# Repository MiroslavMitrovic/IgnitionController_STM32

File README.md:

# IgnitionController_STM32

## Ignition controller implementation for  4T Single Cylinder/V-Twin motorcycle. 

- Generated documentation is available in .\IgnitionController_STM32\Documentation\Ignition_Controller.chm
- Requirements are available in .\IgnitionController_STM32\Design\Requirements\IgnitionControllerRequriements.txt
- Architecture is done with Rational Software architect, and project is available at .\IgnitionController_STM32\Design\

## Addition of CMake build toolchain 
- Command for build configuration generation is : 
cmake -G "Unix Makefiles" -S . -B build -DCMAKE_BUILD_TYPE="Debug" -DCMAKE_TOOLCHAIN_FILE="arm-none-eabi-gcc.cmake" -DCMAKE_EXPORT_COMPILE_COMMANDS=1 
- Command for build is : 
cmake --build build
## Addition of Static and Dynamic Test Frameworks 
- For Static Code Analysis Mathworks Polyspace Code Prover and Bug finder tools are used 
- For Dynamic(Unit) Testing Google Test Framework is used 
- Setup is available in Testing Folder.

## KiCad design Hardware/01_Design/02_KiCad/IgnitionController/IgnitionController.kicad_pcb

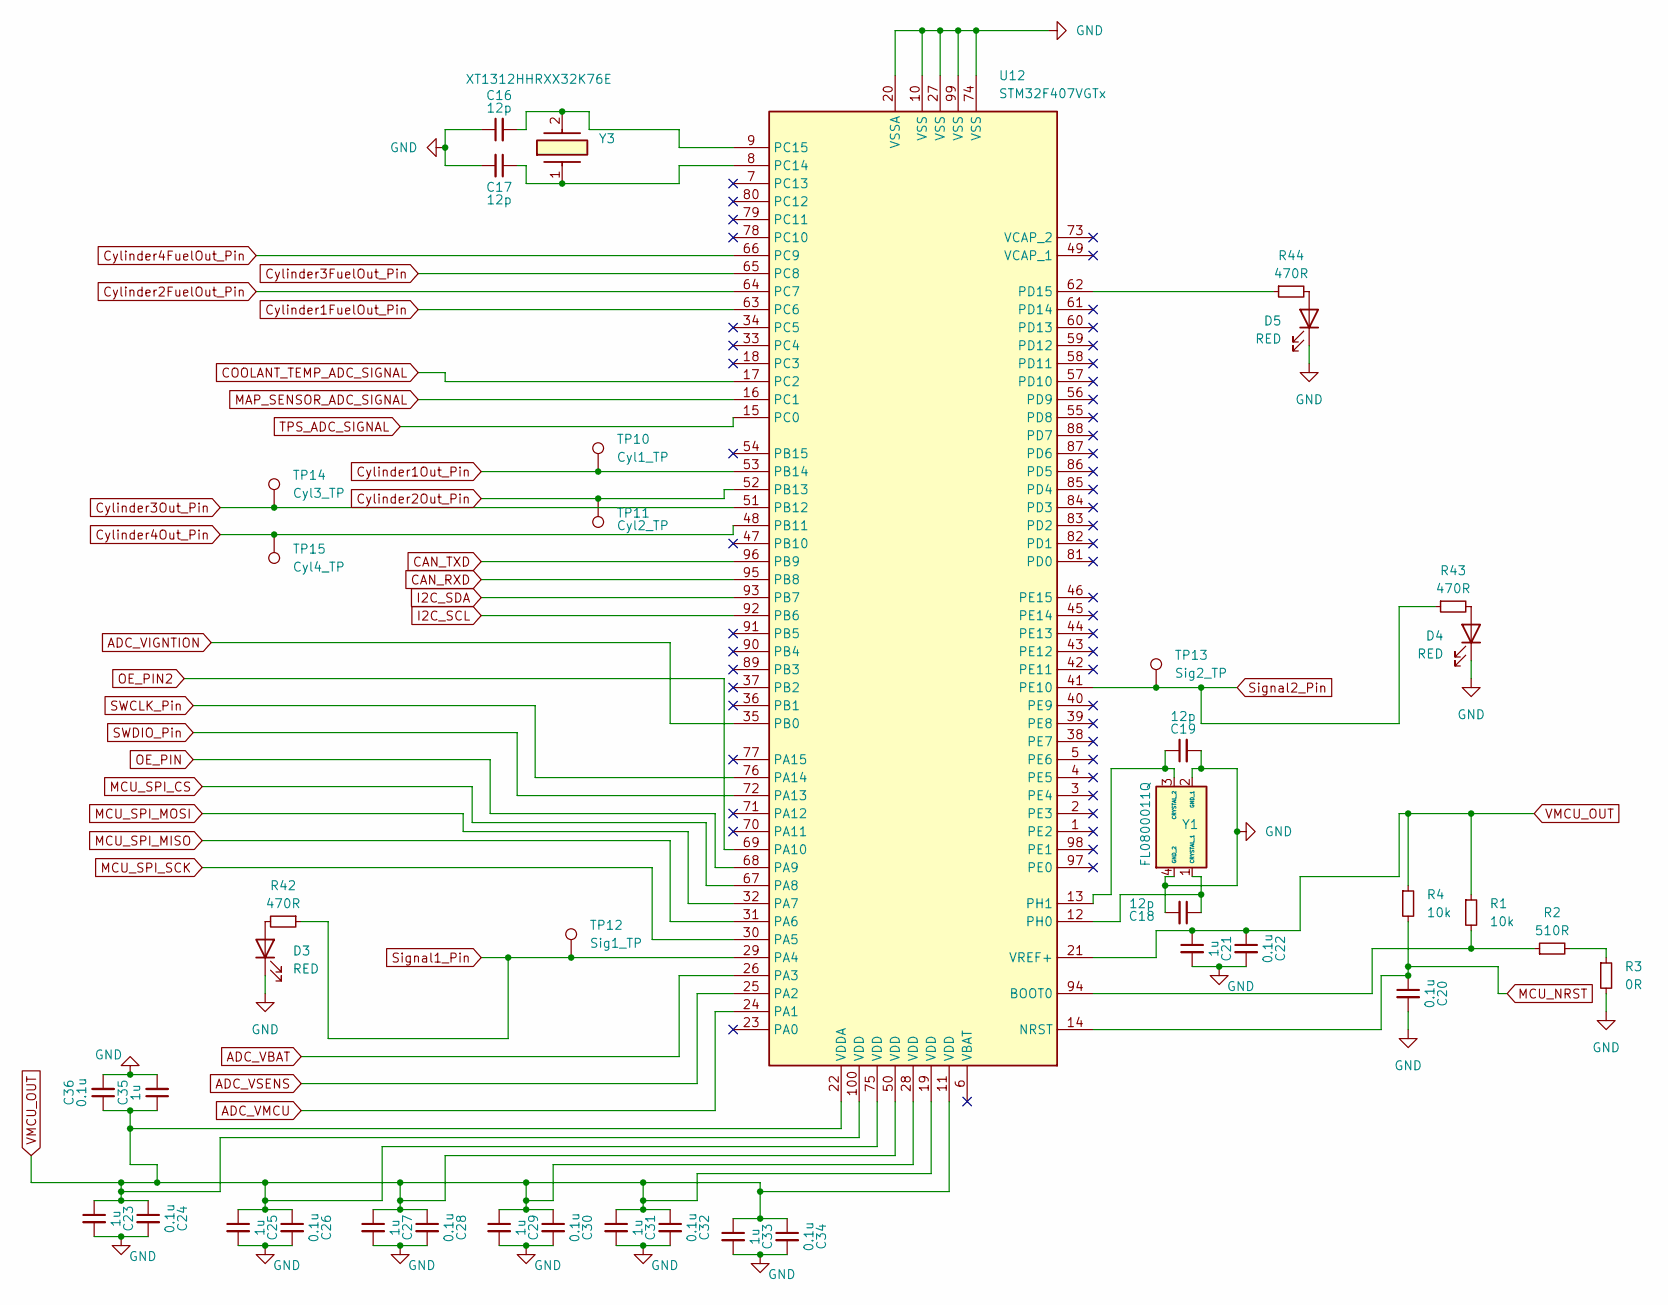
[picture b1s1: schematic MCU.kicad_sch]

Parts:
C16, C17, C18, C19: 12p; C_0603_1608Metric_Pad1.08x0.95mm_HandSolder
C20, C22, C24, C26, C28, C30, C32, C34, C36: 0.1u; C_0603_1608Metric_Pad1.08x0.95mm_HandSolder
C21, C23, C25, C27, C29, C31, C33, C35: 1u; C_0603_1608Metric_Pad1.08x0.95mm_HandSolder
D3, D4, D5: RED; LED_1206_3216Metric_Pad1.42x1.75mm_HandSolder
R1, R4: 10k; R_0603_1608Metric_Pad0.98x0.95mm_HandSolder
R2: 510R; R_0603_1608Metric_Pad0.98x0.95mm_HandSolder
R3: 0R; R_0603_1608Metric_Pad0.98x0.95mm_HandSolder
R42, R43, R44: 470R; R_0603_1608Metric_Pad0.98x0.95mm_HandSolder
TP10: Cyl1_TP; TestPoint_Pad_1.0x1.0mm
TP11: Cyl2_TP; TestPoint_Pad_1.0x1.0mm
TP12: Sig1_TP; TestPoint_Pad_1.0x1.0mm
TP13: Sig2_TP; TestPoint_Pad_1.0x1.0mm
TP14: Cyl3_TP; TestPoint_Pad_1.0x1.0mm
TP15: Cyl4_TP; TestPoint_Pad_1.0x1.0mm
U12: STM32F407VGTx; LQFP-100_14x14mm_P0.5mm
Y1: FL0800011Q; Mouser Part Number 729-FL0800011Q
Y3: XT1312HHRXX32K76E; Mouser Part Number 70-XT1312HHRXX32K76E

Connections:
ADC_VBAT: U12.26 (PA3); also elsewhere on the board
ADC_VIGNTION: U12.35 (PB0); also elsewhere on the board
ADC_VMCU: U12.24 (PA1); also elsewhere on the board
ADC_VSENS: U12.25 (PA2); also elsewhere on the board
CAN_RXD: U12.95 (PB8); also elsewhere on the board
CAN_TXD: U12.96 (PB9); also elsewhere on the board
COOLANT_TEMP_ADC_SIGNAL: U12.17 (PC2); also elsewhere on the board
Cylinder1FuelOut_Pin: U12.63 (PC6); also elsewhere on the board
Cylinder1Out_Pin: TP10.1, U12.53 (PB14); also elsewhere on the board
Cylinder2FuelOut_Pin: U12.64 (PC7); also elsewhere on the board
Cylinder2Out_Pin: TP11.1, U12.52 (PB13); also elsewhere on the board
Cylinder3FuelOut_Pin: U12.65 (PC8); also elsewhere on the board
Cylinder3Out_Pin: TP14.1, U12.51 (PB12); also elsewhere on the board
Cylinder4FuelOut_Pin: U12.66 (PC9); also elsewhere on the board
Cylinder4Out_Pin: TP15.1, U12.48 (PB11); also elsewhere on the board
I2C_SCL: U12.92 (PB6); also elsewhere on the board
I2C_SDA: U12.93 (PB7); also elsewhere on the board
MAP_SENSOR_ADC_SIGNAL: U12.16 (PC1); also elsewhere on the board
MCU_NRST: C20.1, R4.2, U12.14 (NRST); also elsewhere on the board
MCU_SPI_CS: U12.67 (PA8); also elsewhere on the board
MCU_SPI_MISO: U12.31 (PA6); also elsewhere on the board
MCU_SPI_MOSI: U12.32 (PA7); also elsewhere on the board
MCU_SPI_SCK: U12.30 (PA5); also elsewhere on the board
unnamed: D3.2 (A), R42.2
unnamed: D4.2 (A), R43.2
unnamed: D5.2 (A), R44.2
unnamed: R2.2, R3.1
unnamed: R1.2, R2.1, U12.94 (BOOT0)
unnamed: C17.1, U12.8 (PC14), Y3.1
unnamed: C16.2, U12.9 (PC15), Y3.2
unnamed: R44.1, U12.62 (PD15)
unnamed: C19.1, U12.13 (PH1), Y1.3 (CRYSTAL_2)
OE_PIN: U12.68 (PA9); also elsewhere on the board
OE_PIN2: U12.69 (PA10); also elsewhere on the board
SWCLK_Pin: U12.76 (PA14); also elsewhere on the board
SWDIO_Pin: U12.72 (PA13); also elsewhere on the board
Signal1_Pin: R42.1, TP12.1, U12.29 (PA4); also elsewhere on the board
Signal2_Pin: R43.1, TP13.1, U12.41 (PE10); also elsewhere on the board
TPS_ADC_SIGNAL: U12.15 (PC0); also elsewhere on the board

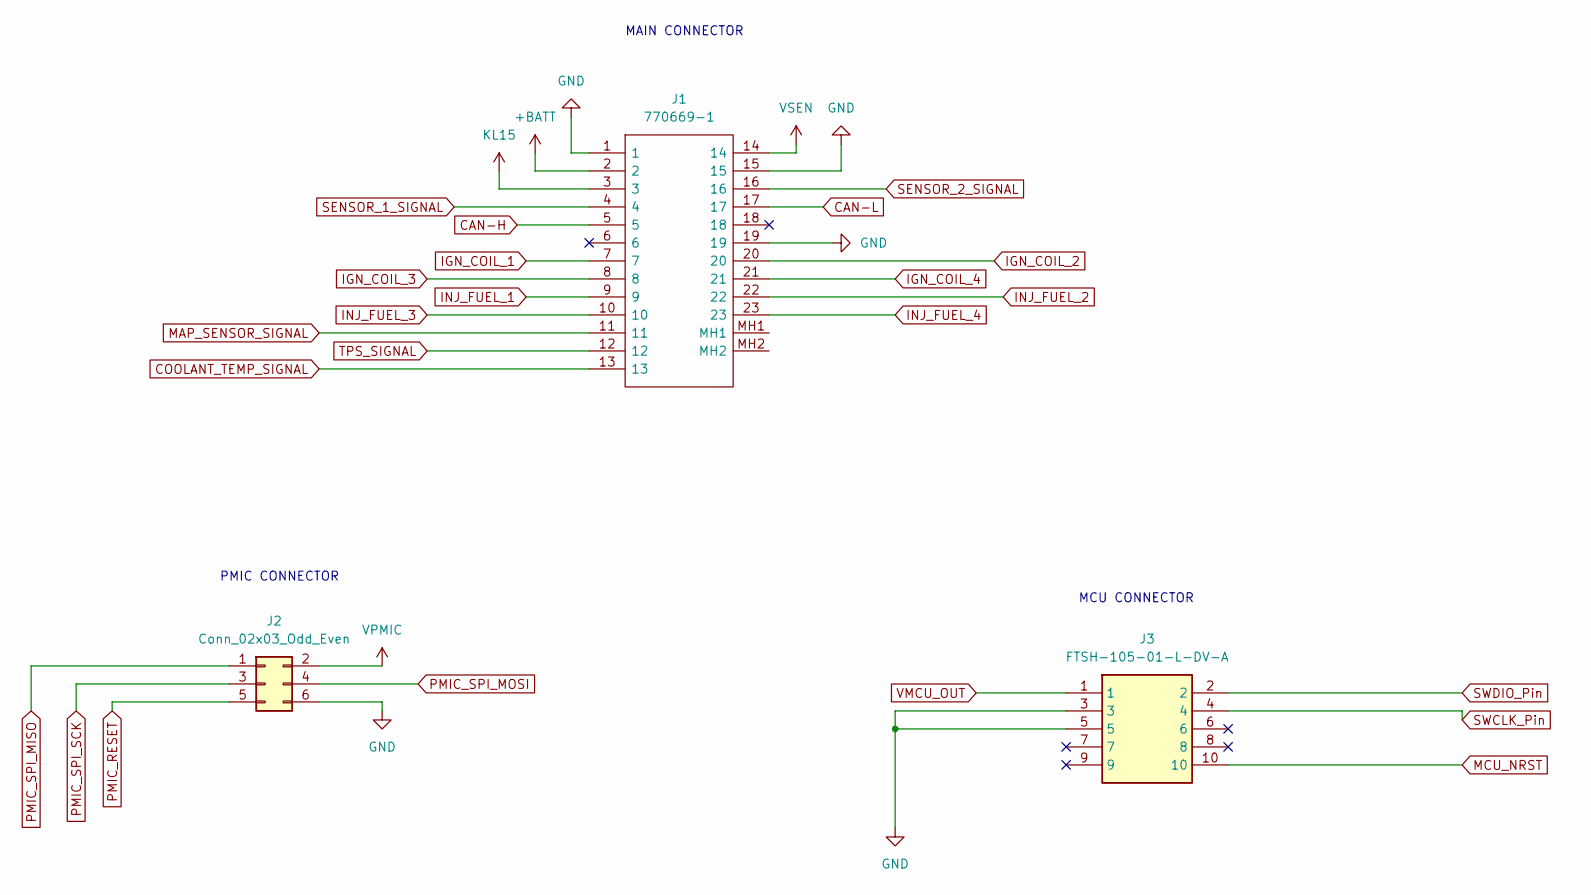
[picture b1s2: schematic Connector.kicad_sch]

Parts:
J1: 770669-1; 7706691; Mouser Part Number 571-770669-1
J2: Conn_02x03_Odd_Even; IDC-Header_2x03_P2.54mm_Vertical
J3: FTSH-105-01-L-DV-A; FTSH-105-XX-YYY-DV-A; Mouser Part Number 200-FTSH10501LDVA

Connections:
+BATT: J1.2; also elsewhere on the board
CAN-H: J1.5; also elsewhere on the board
CAN-L: J1.17; also elsewhere on the board
COOLANT_TEMP_ADC_SIGNAL: J1.13; also elsewhere on the board
IGN_COIL_1: J1.7; also elsewhere on the board
IGN_COIL_2: J1.20; also elsewhere on the board
IGN_COIL_3: J1.8; also elsewhere on the board
IGN_COIL_4: J1.21; also elsewhere on the board
INJ_FUEL_1: J1.9; also elsewhere on the board
INJ_FUEL_2: J1.22; also elsewhere on the board
INJ_FUEL_3: J1.10; also elsewhere on the board
INJ_FUEL_4: J1.23; also elsewhere on the board
MAP_SENSOR_SIGNAL: J1.11; also elsewhere on the board
MCU_NRST: J3.10; also elsewhere on the board
PMIC_RESET: J2.5; also elsewhere on the board
PMIC_SPI_MISO: J2.1; also elsewhere on the board
PMIC_SPI_MOSI: J2.4; also elsewhere on the board
PMIC_SPI_SCK: J2.3; also elsewhere on the board
SENSOR_1_SIGNAL: J1.4; also elsewhere on the board
SENSOR_2_SIGNAL: J1.16; also elsewhere on the board
SWCLK_Pin: J3.4; also elsewhere on the board
SWDIO_Pin: J3.2; also elsewhere on the board
TPS_SIGNAL: J1.12; also elsewhere on the board
VPMIC: J2.2; also elsewhere on the board
VSEN: J1.14; also elsewhere on the board

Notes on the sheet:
MCU CONNECTOR
MAIN CONNECTOR
PMIC CONNECTOR

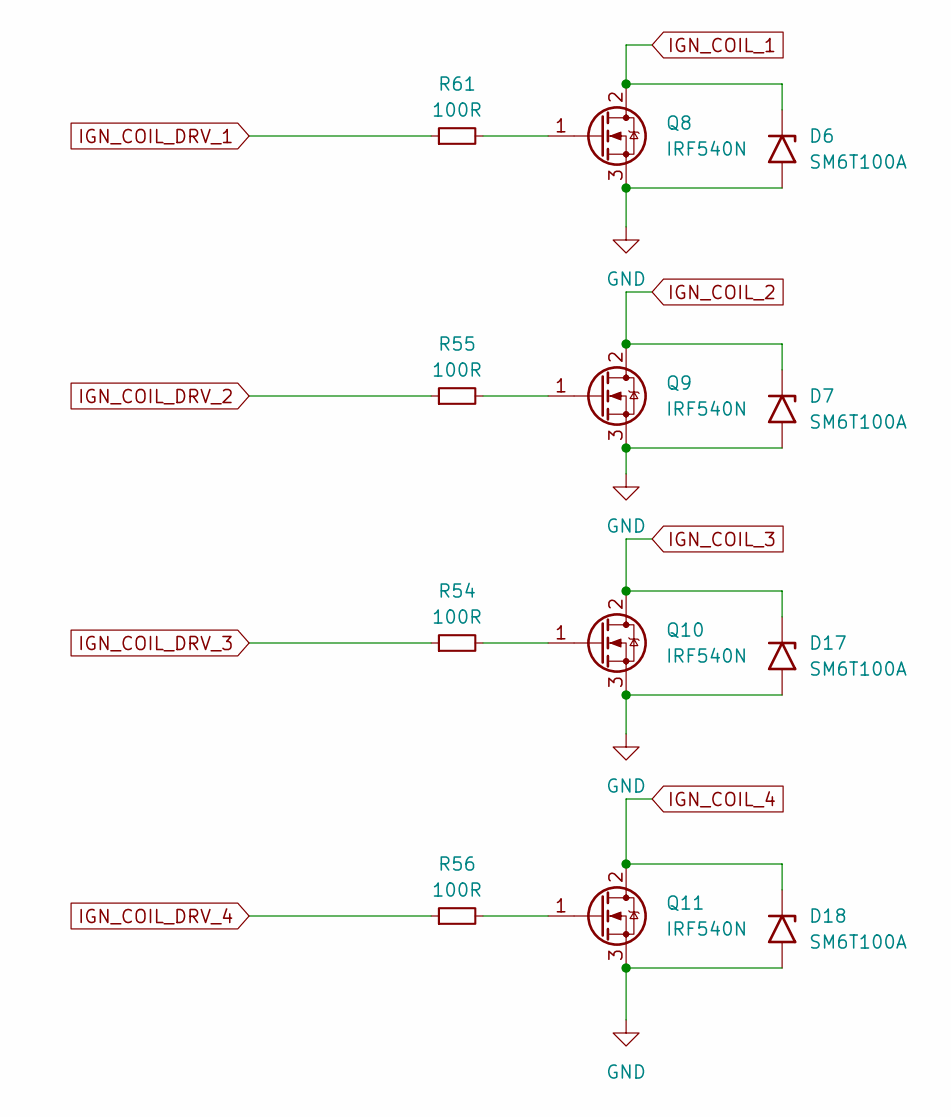
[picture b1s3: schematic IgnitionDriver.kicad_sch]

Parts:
D6, D7, D17, D18: SM6T100A; D_SMB
Q8, Q9, Q10, Q11: IRF540N; TO-220-3_Vertical
R54, R55, R56, R61: 100R; R_0603_1608Metric_Pad0.98x0.95mm_HandSolder

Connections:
IGN_COIL_1: D6.1 (A1), Q8.2 (D); also elsewhere on the board
IGN_COIL_2: D7.1 (A1), Q9.2 (D); also elsewhere on the board
IGN_COIL_3: D17.1 (A1), Q10.2 (D); also elsewhere on the board
IGN_COIL_4: D18.1 (A1), Q11.2 (D); also elsewhere on the board
IGN_COIL_DRV_1: R61.1; also elsewhere on the board
IGN_COIL_DRV_2: R55.1; also elsewhere on the board
IGN_COIL_DRV_3: R54.1; also elsewhere on the board
IGN_COIL_DRV_4: R56.1; also elsewhere on the board
unnamed: Q8.1 (G), R61.2
unnamed: Q9.1 (G), R55.2
unnamed: Q10.1 (G), R54.2
unnamed: Q11.1 (G), R56.2

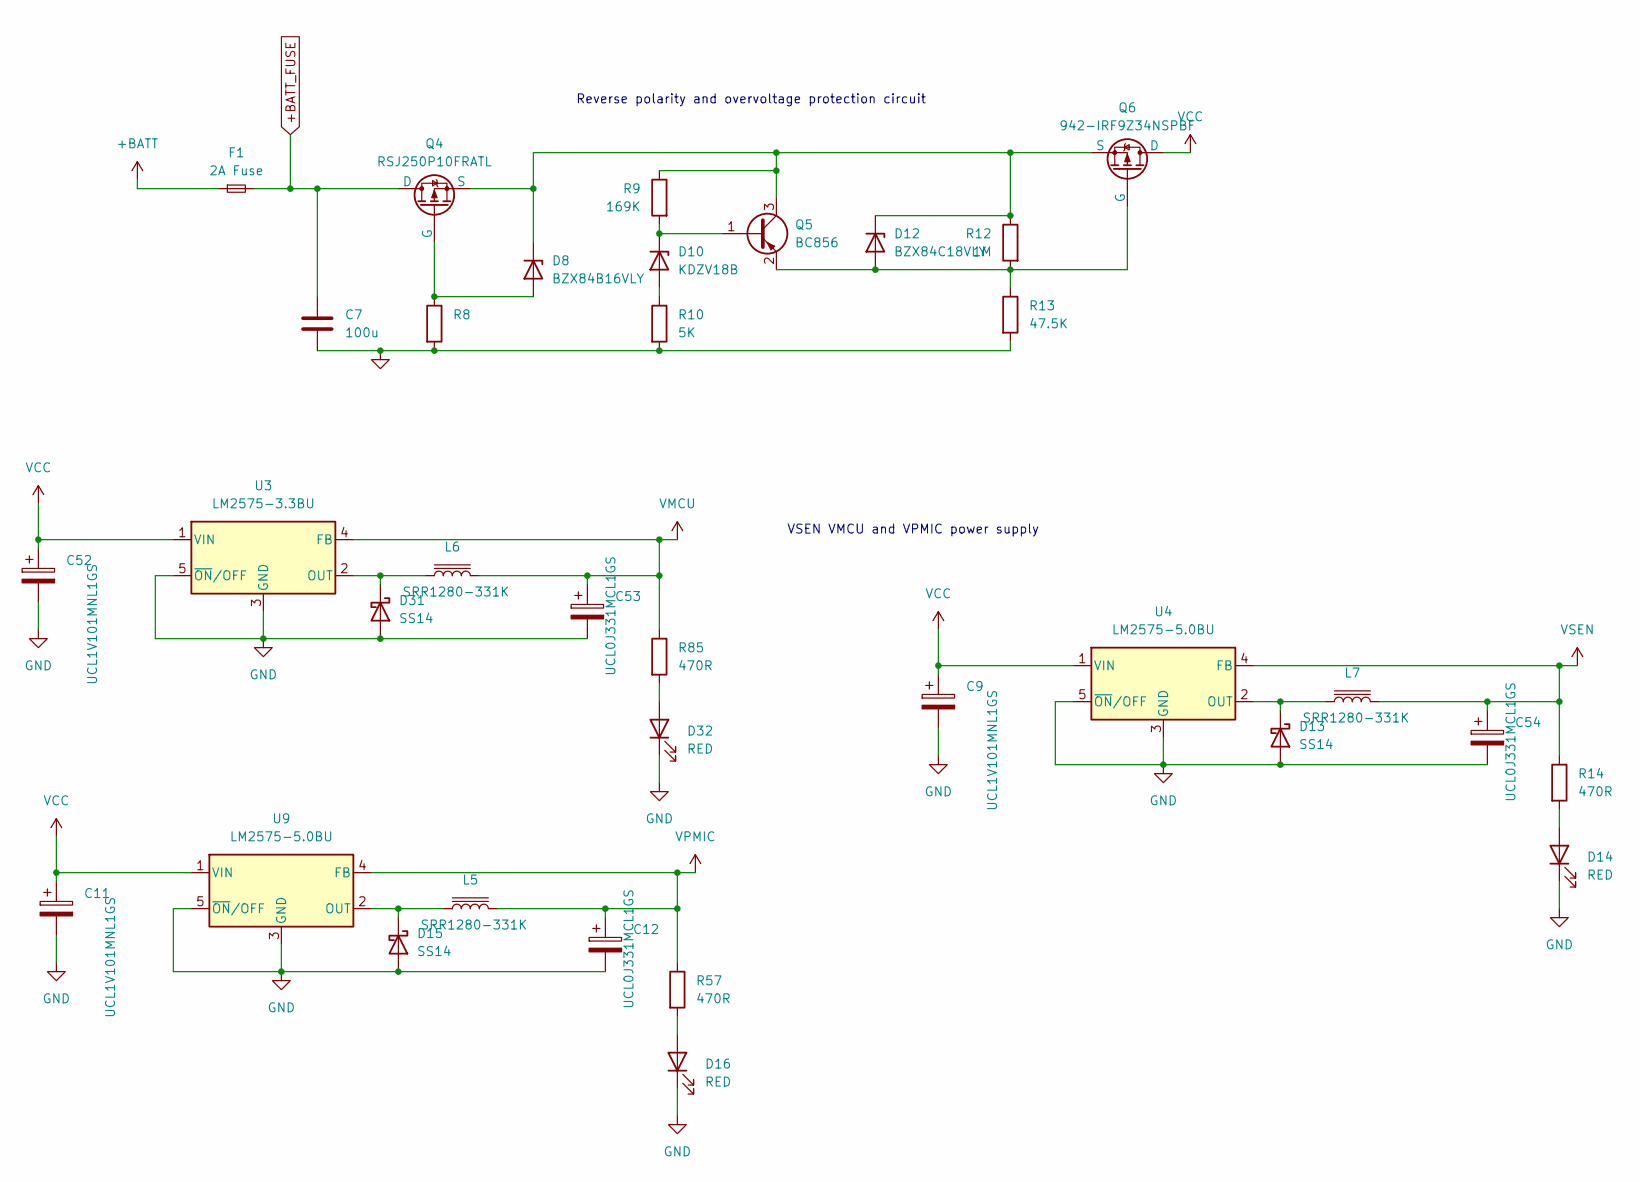
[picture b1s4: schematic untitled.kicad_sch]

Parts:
C7: 100u; C_0603_1608Metric_Pad1.08x0.95mm_HandSolder
C9, C52: UCL1V101MNL1GS; CP_Elec_8x11.9
C11: UCL1V101MNL1GS; CP_Elec_8x11.9; Mouser PN 647-UCL1V101MNL1GS
C12, C53, C54: UCL0J331MCL1GS; CP_Elec_6.3x7.7; Mouser PN 647-UCL0J331MCL1GS
D8: BZX84B16VLY; SOT-23
D10: KDZV18B; D_SOD-123
D12: BZX84C18VLY; SOT-23
D13, D31: SS14; D_SMA
D14, D16, D32: RED; LED_0805_2012Metric_Pad1.15x1.40mm_HandSolder
D15: SS14; D_SMA; Mouser PN 512-SS14
F1: 2A Fuse; Fuse_0805_2012Metric_Pad1.15x1.40mm_HandSolder
L5, L6, L7: SRR1280-331K; L_Bourns_SRR1260; Mouser PN 652-SRR1280-331K
Q4: RSJ250P10FRATL; TO-263-2_Transistor; Mouser PN 755-RSJ250P10FRATL
Q5: BC856; SOT-23
Q6: 942-IRF9Z34NSPBF; TO-263-2_Transistor
R8: 10K; R_0603_1608Metric_Pad0.98x0.95mm_HandSolder
R9: 169K; R_0603_1608Metric_Pad0.98x0.95mm_HandSolder
R10: 5K; R_0603_1608Metric_Pad0.98x0.95mm_HandSolder
R12: 1M; R_0603_1608Metric_Pad0.98x0.95mm_HandSolder
R13: 47.5K; R_0603_1608Metric_Pad0.98x0.95mm_HandSolder
R14, R57, R85: 470R; R_0603_1608Metric_Pad0.98x0.95mm_HandSolder
U3: LM2575-3.3BU; TO-263-5_TabPin3
U4: LM2575-5.0BU; TO-263-5_TabPin3
U9: LM2575-5.0BU; TO-263-5_TabPin3; Mouser PN 998-LM2575-5.0WU

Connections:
+BATT: F1.1; also elsewhere on the board
unnamed: D8.1 (A), Q4.1 (G), R8.1
unnamed: D10.2 (A), R10.1
unnamed: D10.1 (K), Q5.1 (B), R9.2
unnamed: D12.1 (A), Q5.2 (E), Q6.1 (G), R12.2, R13.1
unnamed: D8.3 (K), D12.3 (K), Q4.3 (S), Q5.3 (C), Q6.3 (S), R9.1, R12.1
unnamed: D13.1 (K), L7.1, U4.2 (OUT)
unnamed: D14.2 (A), R14.2
unnamed: D15.1 (K), L5.1, U9.2 (OUT)
unnamed: D16.2 (A), R57.2
unnamed: D31.1 (K), L6.1, U3.2 (OUT)
unnamed: D32.2 (A), R85.2
VCC: C9.1, C11.1, C52.1, Q6.2 (D), U3.1 (VIN), U4.1 (VIN), U9.1 (VIN)
VPMIC: C12.1, L5.2, R57.1, U9.4 (FB); also elsewhere on the board
VSEN: C54.1, L7.2, R14.1, U4.4 (FB); also elsewhere on the board

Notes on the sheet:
VSEN VMCU and VPMIC power supply
Reverse polarity and overvoltage protection circuit

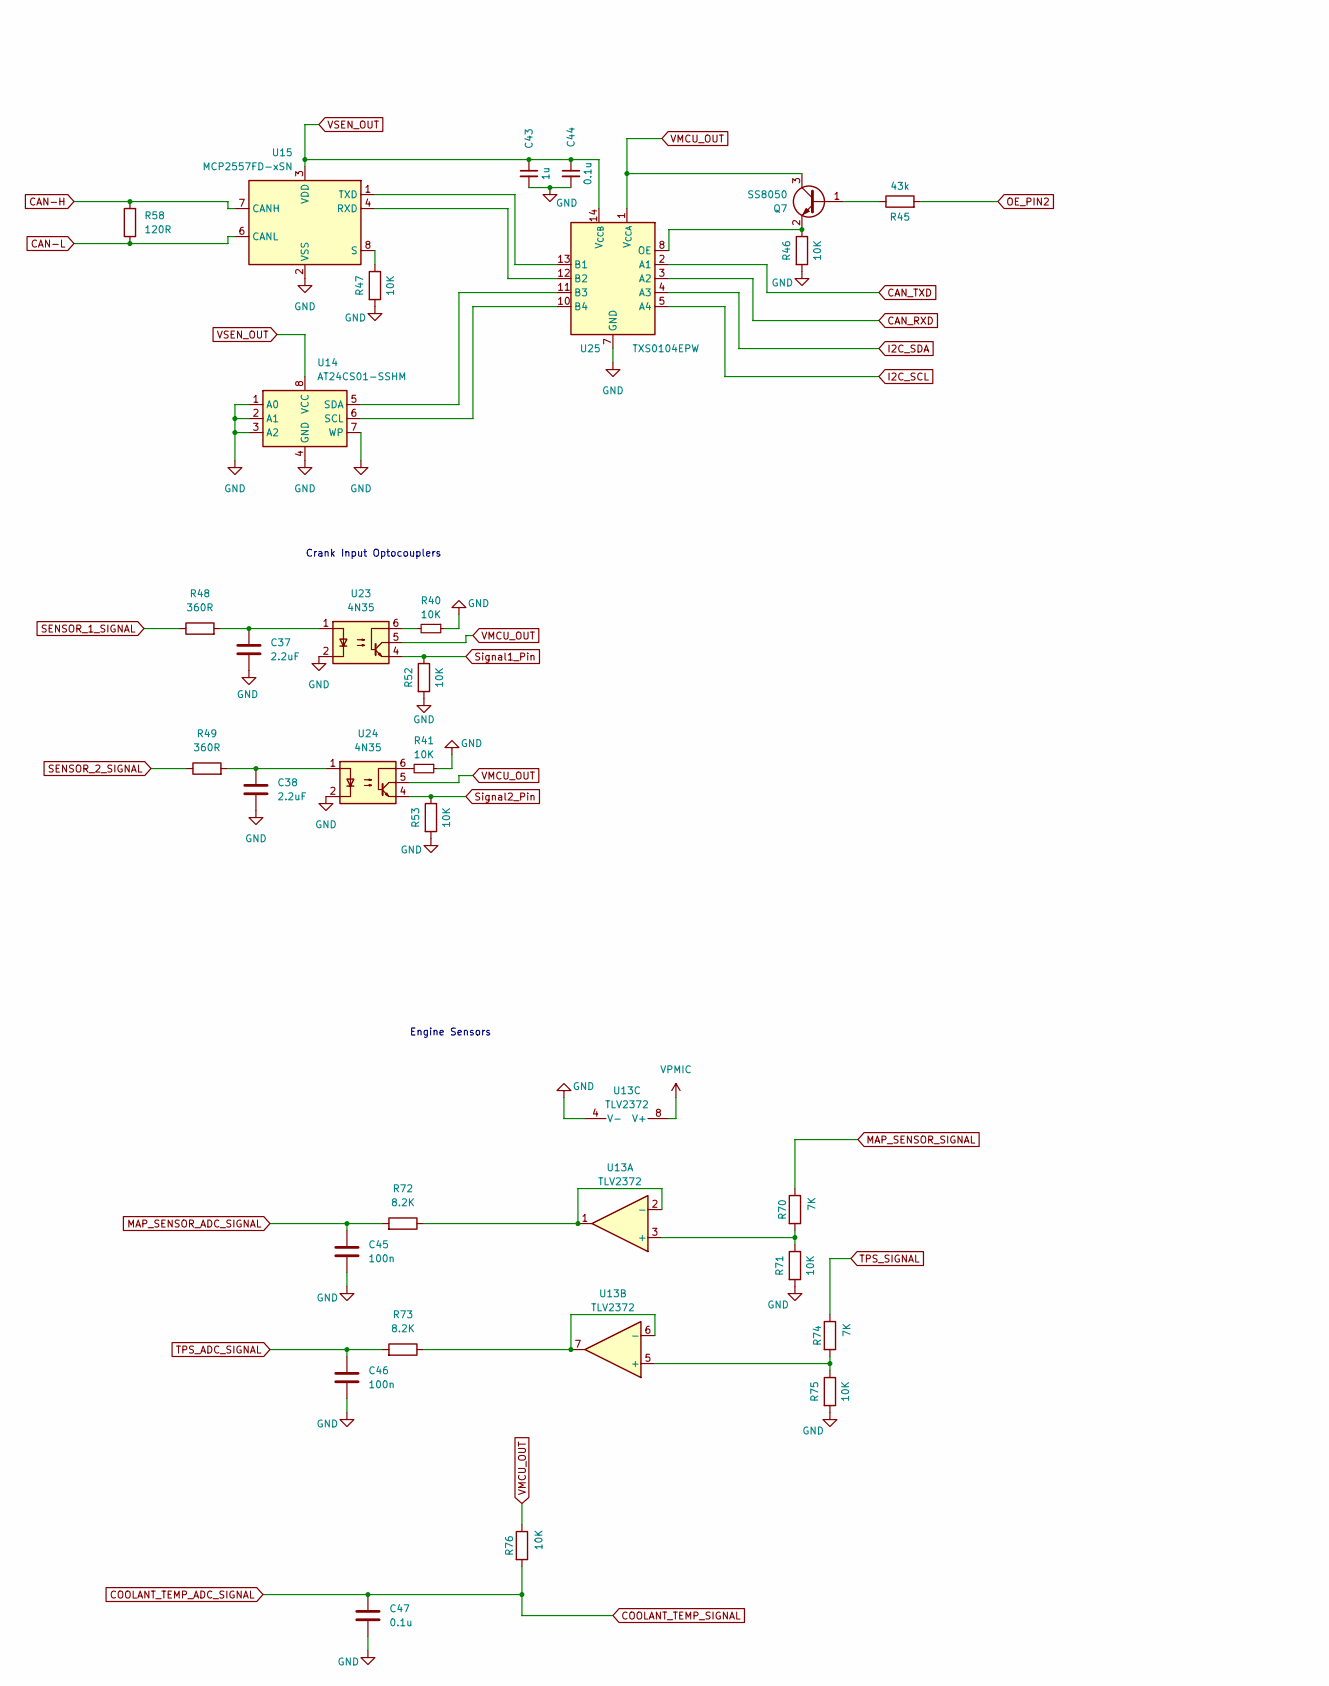
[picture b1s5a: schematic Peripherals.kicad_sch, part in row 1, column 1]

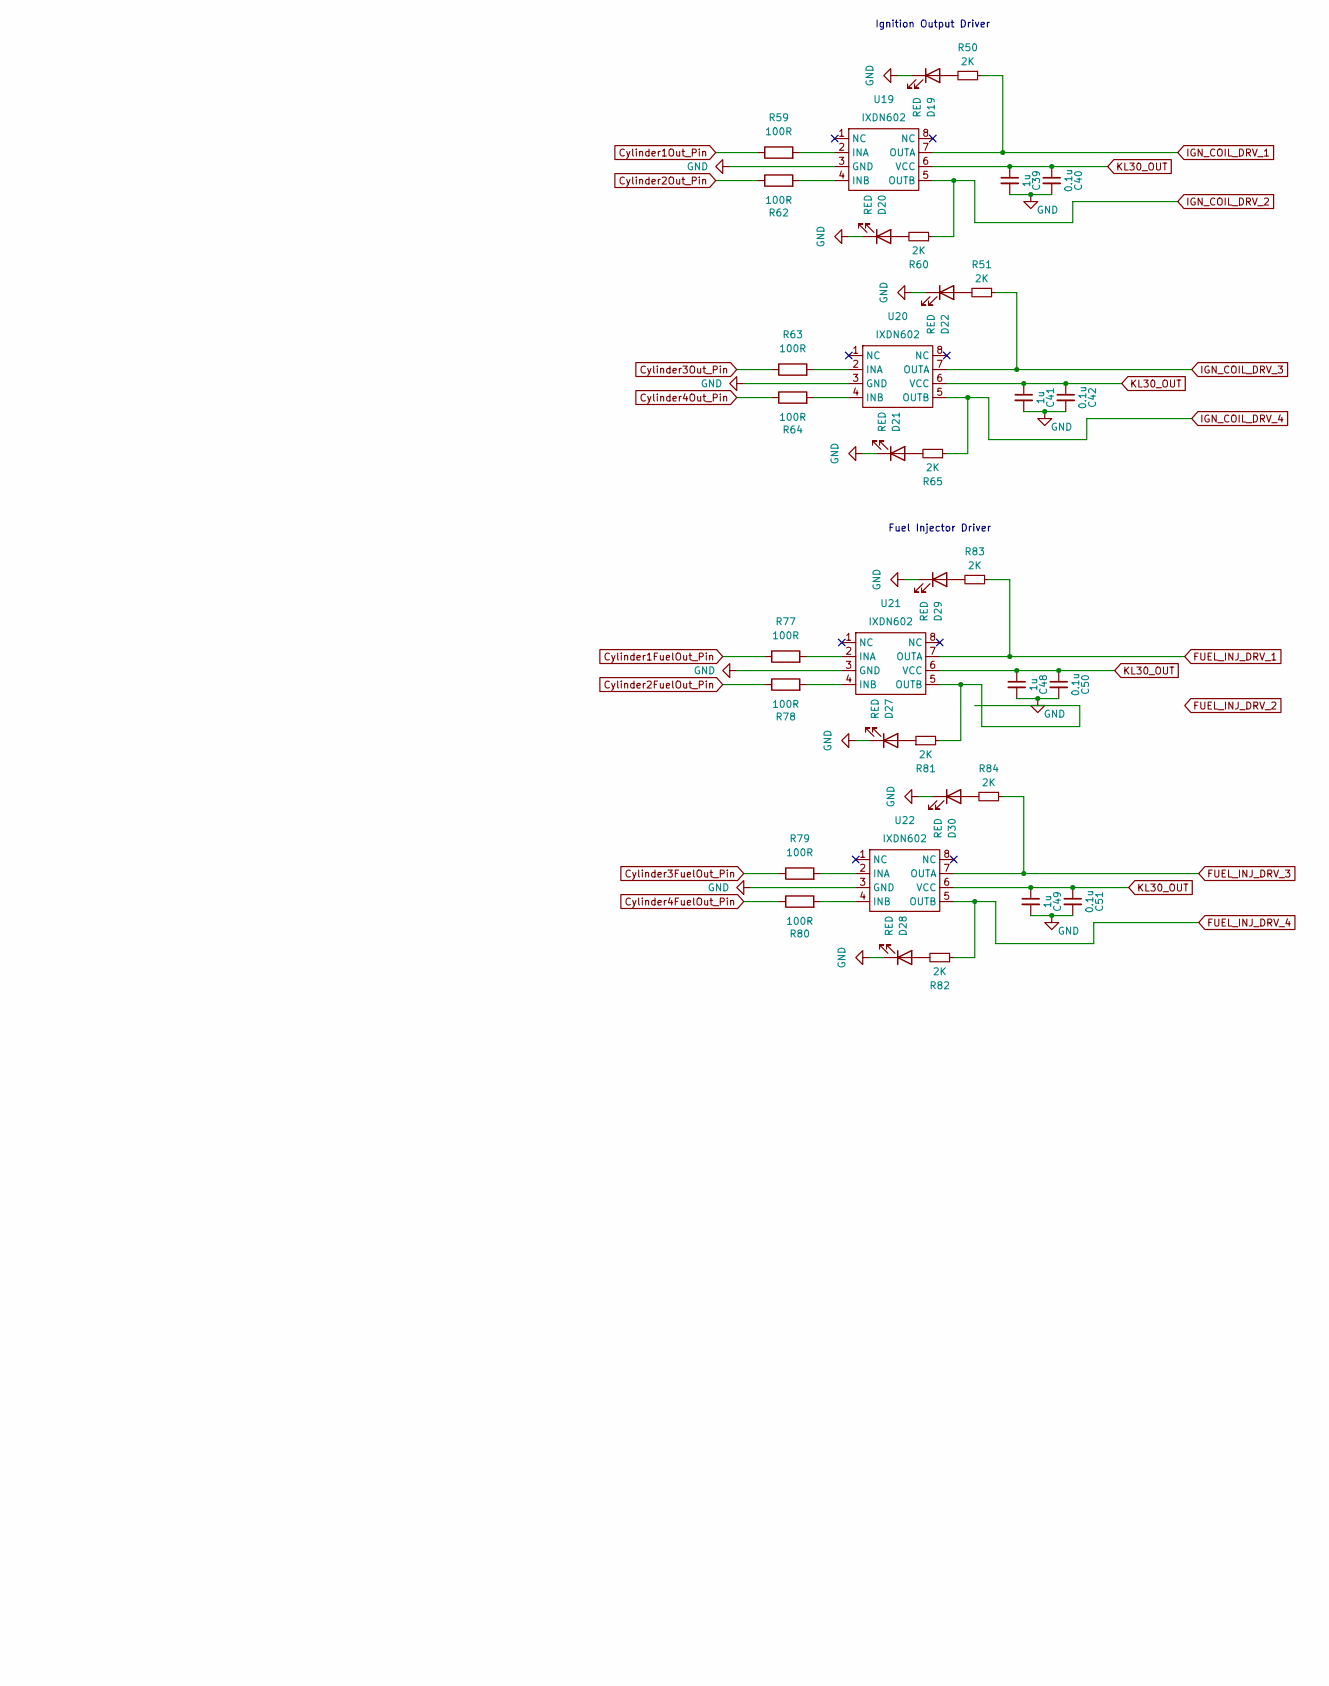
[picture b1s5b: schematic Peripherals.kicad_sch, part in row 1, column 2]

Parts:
C37, C38: 2.2uF; C_0603_1608Metric_Pad1.08x0.95mm_HandSolder
C39, C41, C43, C48, C49: 1u; C_0603_1608Metric_Pad1.08x0.95mm_HandSolder
C40, C42, C44, C47, C50, C51: 0.1u; C_0603_1608Metric_Pad1.08x0.95mm_HandSolder
C45, C46: 100n; C_0603_1608Metric_Pad1.08x0.95mm_HandSolder
D19, D20, D21, D22, D27, D28, D29, D30: RED; LED_1206_3216Metric_Pad1.42x1.75mm_HandSolder
Q7: SS8050; TSOT-23_HandSoldering
R40, R41, R46, R47, R52, R53, R71, R75, R76: 10K; R_0603_1608Metric_Pad0.98x0.95mm_HandSolder
R45: 43k; R_0603_1608Metric_Pad0.98x0.95mm_HandSolder
R48, R49: 360R; R_0603_1608Metric_Pad0.98x0.95mm_HandSolder
R50, R51, R60, R65, R81, R82, R83, R84: 2K; R_0603_1608Metric_Pad0.98x0.95mm_HandSolder
R58: 120R; R_0603_1608Metric_Pad0.98x0.95mm_HandSolder
R59, R62, R63, R64, R77, R78, R79, R80: 100R; R_0603_1608Metric_Pad0.98x0.95mm_HandSolder
R70, R74: 7K; R_0603_1608Metric_Pad0.98x0.95mm_HandSolder
R72, R73: 8.2K; R_0603_1608Metric_Pad0.98x0.95mm_HandSolder
U13: TLV2372; SOIC-8_5.3x6.2mm_P1.27mm
U14: AT24CS01-SSHM; SOIC-8_3.9x4.9mm_P1.27mm
U15: MCP2557FD-xSN; SOIC-8_3.9x4.9mm_P1.27mm
U19, U20, U21, U22: IXDN602; SO-8_3.9x4.9mm_P1.27mm
U23, U24: 4N35; 4N35S
U25: TXS0104EPW; TSSOP-14_4.4x5mm_P0.65mm

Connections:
CAN-H: R58.2, U15.7 (CANH); also elsewhere on the board
CAN-L: R58.1, U15.6 (CANL); also elsewhere on the board
CAN_RXD: U25.3 (A2); also elsewhere on the board
CAN_TXD: U25.2 (A1); also elsewhere on the board
COOLANT_TEMP_ADC_SIGNAL: C47.1, R76.2; also elsewhere on the board
Cylinder1FuelOut_Pin: R77.1; also elsewhere on the board
Cylinder1Out_Pin: R59.1; also elsewhere on the board
Cylinder2FuelOut_Pin: R78.1; also elsewhere on the board
Cylinder2Out_Pin: R62.1; also elsewhere on the board
Cylinder3FuelOut_Pin: R79.1; also elsewhere on the board
Cylinder3Out_Pin: R63.1; also elsewhere on the board
Cylinder4FuelOut_Pin: R80.1; also elsewhere on the board
Cylinder4Out_Pin: R64.1; also elsewhere on the board
FUEL_INJ_DRV_1: R83.1, U21.7 (OUTA); also elsewhere on the board
FUEL_INJ_DRV_3: R84.1, U22.7 (OUTA); also elsewhere on the board
FUEL_INJ_DRV_4: R82.1, U22.5 (OUTB); also elsewhere on the board
I2C_SCL: U25.5 (A4); also elsewhere on the board
I2C_SDA: U25.4 (A3); also elsewhere on the board
IGN_COIL_DRV_1: R50.1, U19.7 (OUTA); also elsewhere on the board
IGN_COIL_DRV_2: R60.1, U19.5 (OUTB); also elsewhere on the board
IGN_COIL_DRV_3: R51.1, U20.7 (OUTA); also elsewhere on the board
IGN_COIL_DRV_4: R65.1, U20.5 (OUTB); also elsewhere on the board
KL30_OUT: C39.1, C40.1, C41.1, C42.1, C48.1, C49.1, C50.1, C51.1, U19.6 (VCC), U20.6 (VCC), U21.6 (VCC), U22.6 (VCC); also elsewhere on the board
MAP_SENSOR_ADC_SIGNAL: C45.1, R72.2; also elsewhere on the board
MAP_SENSOR_SIGNAL: R70.1; also elsewhere on the board
unnamed: C37.1, R48.2, U23.1
unnamed: C38.1, R49.2, U24.1
unnamed: D19.2 (A), R50.2
unnamed: D20.2 (A), R60.2
unnamed: D21.2 (A), R65.2
unnamed: D22.2 (A), R51.2
unnamed: D27.2 (A), R81.1
unnamed: D28.2 (A), R82.2
unnamed: D29.2 (A), R83.2
unnamed: D30.2 (A), R84.2
unnamed: Q7.1 (B), R45.1
unnamed: Q7.2 (E), R46.1, U25.8 (OE)
unnamed: R40.2, U23.6
unnamed: R41.2, U24.6
unnamed: R70.2, R71.1, U13.3 (+)
unnamed: R72.1, U13.1, U13.2 (-)
unnamed: R74.2, R75.1, U13.5 (+)
unnamed: R73.1, U13.6 (-), U13.7
unnamed: U14.6 (SCL), U25.10 (B4)
unnamed: U14.5 (SDA), U25.11 (B3)
unnamed: U15.4 (RXD), U25.12 (B2)
unnamed: R47.1, U15.8 (S)
unnamed: U15.1 (TXD), U25.13 (B1)
unnamed: R59.2, U19.2 (INA)
unnamed: R62.2, U19.4 (INB)
unnamed: R63.2, U20.2 (INA)
unnamed: R64.2, U20.4 (INB)
unnamed: R77.2, U21.2 (INA)
unnamed: R78.2, U21.4 (INB)
unnamed: R81.2, U21.5 (OUTB)
unnamed: R79.2, U22.2 (INA)
unnamed: R80.2, U22.4 (INB)
OE_PIN2: R45.2; also elsewhere on the board
SENSOR_1_SIGNAL: R48.1; also elsewhere on the board
SENSOR_2_SIGNAL: R49.1; also elsewhere on the board
Signal1_Pin: R52.1, U23.4; also elsewhere on the board
Signal2_Pin: R53.1, U24.4; also elsewhere on the board
TPS_ADC_SIGNAL: C46.1, R73.2; also elsewhere on the board
TPS_SIGNAL: R74.1; also elsewhere on the board
VPMIC: U13.8 (V+); also elsewhere on the board
VSEN_OUT: C43.1, C44.1, U14.8 (VCC), U15.3 (VDD), U25.14 (V_{CCB}); also elsewhere on the board

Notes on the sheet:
Crank Input Optocouplers
Fuel Injector Driver
Engine Sensors
Ignition Output Driver

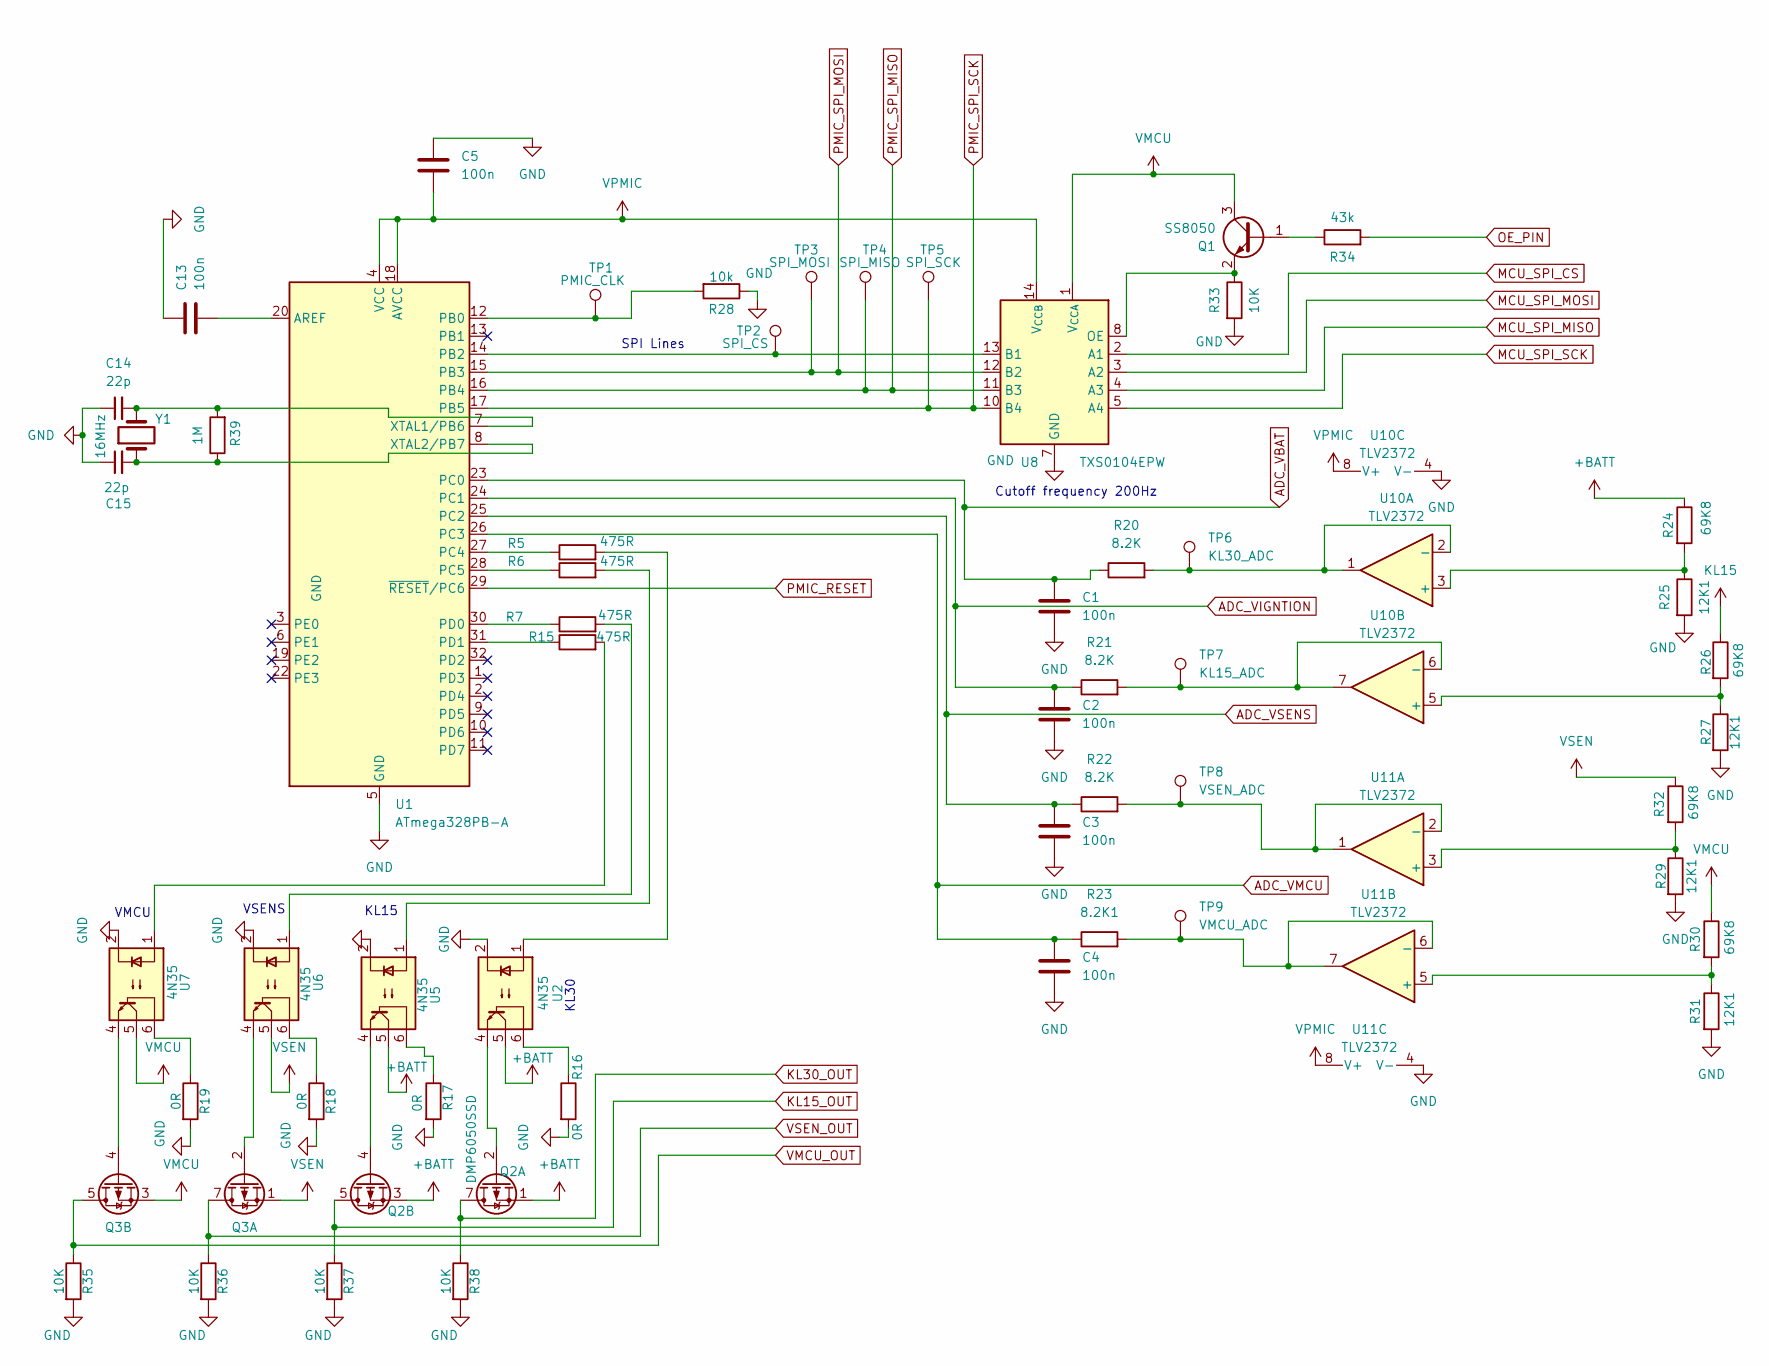
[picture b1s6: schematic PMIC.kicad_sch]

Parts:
C1, C2, C3, C4, C5, C13: 100n; C_0603_1608Metric_Pad1.08x0.95mm_HandSolder
C14, C15: 22p; C_0603_1608Metric_Pad1.08x0.95mm_HandSolder
Q1: SS8050; TSOT-23_HandSoldering
Q2, Q3: DMP6050SSD; SOIC-8_3.9x4.9mm_P1.27mm
R5, R6, R7, R15: 475R; R_0603_1608Metric_Pad0.98x0.95mm_HandSolder
R16, R17, R18, R19: 0R; R_0603_1608Metric_Pad0.98x0.95mm_HandSolder
R20, R21, R22: 8.2K; R_0603_1608Metric_Pad0.98x0.95mm_HandSolder
R23: 8.2K1; R_0603_1608Metric_Pad0.98x0.95mm_HandSolder
R24, R26, R30, R32: 69K8; R_0603_1608Metric_Pad0.98x0.95mm_HandSolder
R25, R27, R29, R31: 12K1; R_0603_1608Metric_Pad0.98x0.95mm_HandSolder
R28: 10k; R_0603_1608Metric_Pad0.98x0.95mm_HandSolder
R33, R35, R36, R37, R38: 10K; R_0603_1608Metric_Pad0.98x0.95mm_HandSolder
R34: 43k; R_0603_1608Metric_Pad0.98x0.95mm_HandSolder
R39: 1M; R_0603_1608Metric_Pad0.98x0.95mm_HandSolder
TP1: PMIC_CLK; TestPoint_Pad_1.0x1.0mm
TP2: SPI_CS; TestPoint_Pad_1.0x1.0mm
TP3: SPI_MOSI; TestPoint_Pad_1.0x1.0mm
TP4: SPI_MISO; TestPoint_Pad_1.0x1.0mm
TP5: SPI_SCK; TestPoint_Pad_1.0x1.0mm
TP6: KL30_ADC; TestPoint_Pad_1.0x1.0mm
TP7: KL15_ADC; TestPoint_Pad_1.0x1.0mm
TP8: VSEN_ADC; TestPoint_Pad_1.0x1.0mm
TP9: VMCU_ADC; TestPoint_Pad_1.0x1.0mm
U1: ATmega328PB-A; TQFP-32_7x7mm_P0.8mm
U2, U5, U6, U7: 4N35; 4N35S
U8: TXS0104EPW; TSSOP-14_4.4x5mm_P0.65mm
U10, U11: TLV2372; SOIC-8_5.3x6.2mm_P1.27mm
Y1: 16MHz; Crystal_HC52-8mm_Horizontal

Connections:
ADC_VBAT: C1.1, R20.1, U1.23 (PC0); also elsewhere on the board
ADC_VIGNTION: C2.1, R21.1, U1.24 (PC1); also elsewhere on the board
ADC_VMCU: C4.1, R23.1, U1.26 (PC3); also elsewhere on the board
ADC_VSENS: C3.1, R22.1, U1.25 (PC2); also elsewhere on the board
KL15_OUT: Q2.5 (D2), Q2.6 (D2), R37.1
KL30_OUT: Q2.7 (D1), Q2.8 (D1), R38.1; also elsewhere on the board
MCU_SPI_CS: U8.2 (A1); also elsewhere on the board
MCU_SPI_MISO: U8.4 (A3); also elsewhere on the board
MCU_SPI_MOSI: U8.3 (A2); also elsewhere on the board
MCU_SPI_SCK: U8.5 (A4); also elsewhere on the board
unnamed: Q1.1 (B), R34.1
unnamed: Q1.2 (E), R33.1, U8.8 (OE)
unnamed: Q2.2 (G1), U2.4
unnamed: Q2.4 (G2), U5.4
unnamed: Q3.2 (G1), U6.4
unnamed: Q3.4 (G2), U7.4
unnamed: R5.2, U2.1
unnamed: R6.2, U5.1
unnamed: R7.2, U6.1
unnamed: R15.2, U7.1
unnamed: R16.1, U2.6
unnamed: R17.1, U5.6
unnamed: R18.1, U6.6
unnamed: R19.1, U7.6
unnamed: C13.2, U1.20 (AREF)
unnamed: R28.2, TP1.1, U1.12 (PB0)
unnamed: TP2.1, U1.14 (PB2), U8.13 (B1)
unnamed: R5.1, U1.27 (PC4)
unnamed: R6.1, U1.28 (PC5)
unnamed: R7.1, U1.30 (PD0)
unnamed: R15.1, U1.31 (PD1)
unnamed: R24.2, R25.1, U10.3 (+)
unnamed: R20.2, TP6.1, U10.1, U10.2 (-)
unnamed: R26.2, R27.1, U10.5 (+)
unnamed: R21.2, TP7.1, U10.6 (-), U10.7
unnamed: R29.1, R32.2, U11.3 (+)
unnamed: R22.2, TP8.1, U11.1, U11.2 (-)
unnamed: R30.2, R31.1, U11.5 (+)
unnamed: R23.2, TP9.1, U11.6 (-), U11.7
OE_PIN: R34.2; also elsewhere on the board
PMIC_RESET: U1.29 (~RESET/PC6); also elsewhere on the board
PMIC_SPI_MISO: TP4.1, U1.16 (PB4), U8.11 (B3); also elsewhere on the board
PMIC_SPI_MOSI: TP3.1, U1.15 (PB3), U8.12 (B2); also elsewhere on the board
PMIC_SPI_SCK: TP5.1, U1.17 (PB5), U8.10 (B4); also elsewhere on the board
VPMIC: C5.2, U1.4 (VCC), U1.18 (AVCC), U8.14 (V_{CCB}), U10.8 (V+), U11.8 (V+); also elsewhere on the board
VSEN: Q3.1 (S1), R32.1, U6.5; also elsewhere on the board
VSEN_OUT: Q3.7 (D1), Q3.8 (D1), R36.1; also elsewhere on the board

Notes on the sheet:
KL15
Cutoff frequency 200Hz
VMCU
KL30
SPI Lines
VSENS
